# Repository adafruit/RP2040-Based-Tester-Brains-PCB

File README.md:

## Adafruit RP2040 Based Tester Brains PCB

PCB files for the Adafruit RP2040 Based Tester Brains. 

Format is EagleCAD schematic and board layout

### Description

This board is what we use internally at Adafruit to program and test boards with microcontrollers on them. 
   * An [RP2040 Pico](https://www.adafruit.com/product/5525) (or perhaps PicoW?) is used to run the test software
   * [Use a 16x2 LCD (ideally RGB backlight)](https://www.adafruit.com/product/398) for display output with color feedback such as green for pass, red for fail. RGB backlight is WS2811-controlled. Don't forget to set the contrast pot on first usage.
   * Serial1 hardware UART has RX/TX pin switch to flip directions
   * 1.9" TFT connector is placed but hasn't been tested or used yet
   * Piezo buzzer can be used for audible feedback alerts
   * STEMMA QT I2C port
   * Big reset button
   * Firmware files can be stored on MicroSD card which is slotted in. 
   * Connect the right hand side, either the 0.1" header or 18-pin EYESPI-like FPC connector to the device-under-test jig which can be different for each product. 
   * [USB Host testing is done with bitbang PIO support in TinyUSB](https://github.com/adafruit/Adafruit_TinyUSB_Arduino), USB 5V power can be turned on / off 
   * Use Philhower RP2040 core for programming
   * The RP2040 brains can perform ESP32 programming, RP2040-via-USB, AVR ICSP/UPDI, or SWD DAP. [See the TestBed library for some examples.](https://github.com/adafruit/Adafruit_TestBed)

**THIS IS NOT AN ADAFRUIT PRODUCT, IT IS COMPLETELY AND UTTERLY UNSUPPORTED. THERE ARE NO PLANS/ETA FOR MANUFACTURING, STOCKING OR SUPPORTING. DO NOT ASK FOR SUPPORT OR ASSISTANCE. THIS INCLUDES ASKING US FOR BOM, SOURCING OR ASSEMBLY HELP. WE DON'T GUARANTEE IT WORKS FOR YOU OR AT ALL AND ARE ONLY PUBLISHING IT IN THE HOPES THAT IT IS USEFUL FOR SOMEONE WHO DOES NOT NEED SUPPORT OR ASSISTANCE IN USING IT!**

### License

Adafruit invests time and resources providing this open source design, please support Adafruit and open-source hardware by purchasing products from [Adafruit](https://www.adafruit.com)!

Designed by Limor Fried/Ladyada for Adafruit Industries.

Creative Commons Attribution/Share-Alike, all text above must be included in any redistribution. 
See license.txt for additional details.

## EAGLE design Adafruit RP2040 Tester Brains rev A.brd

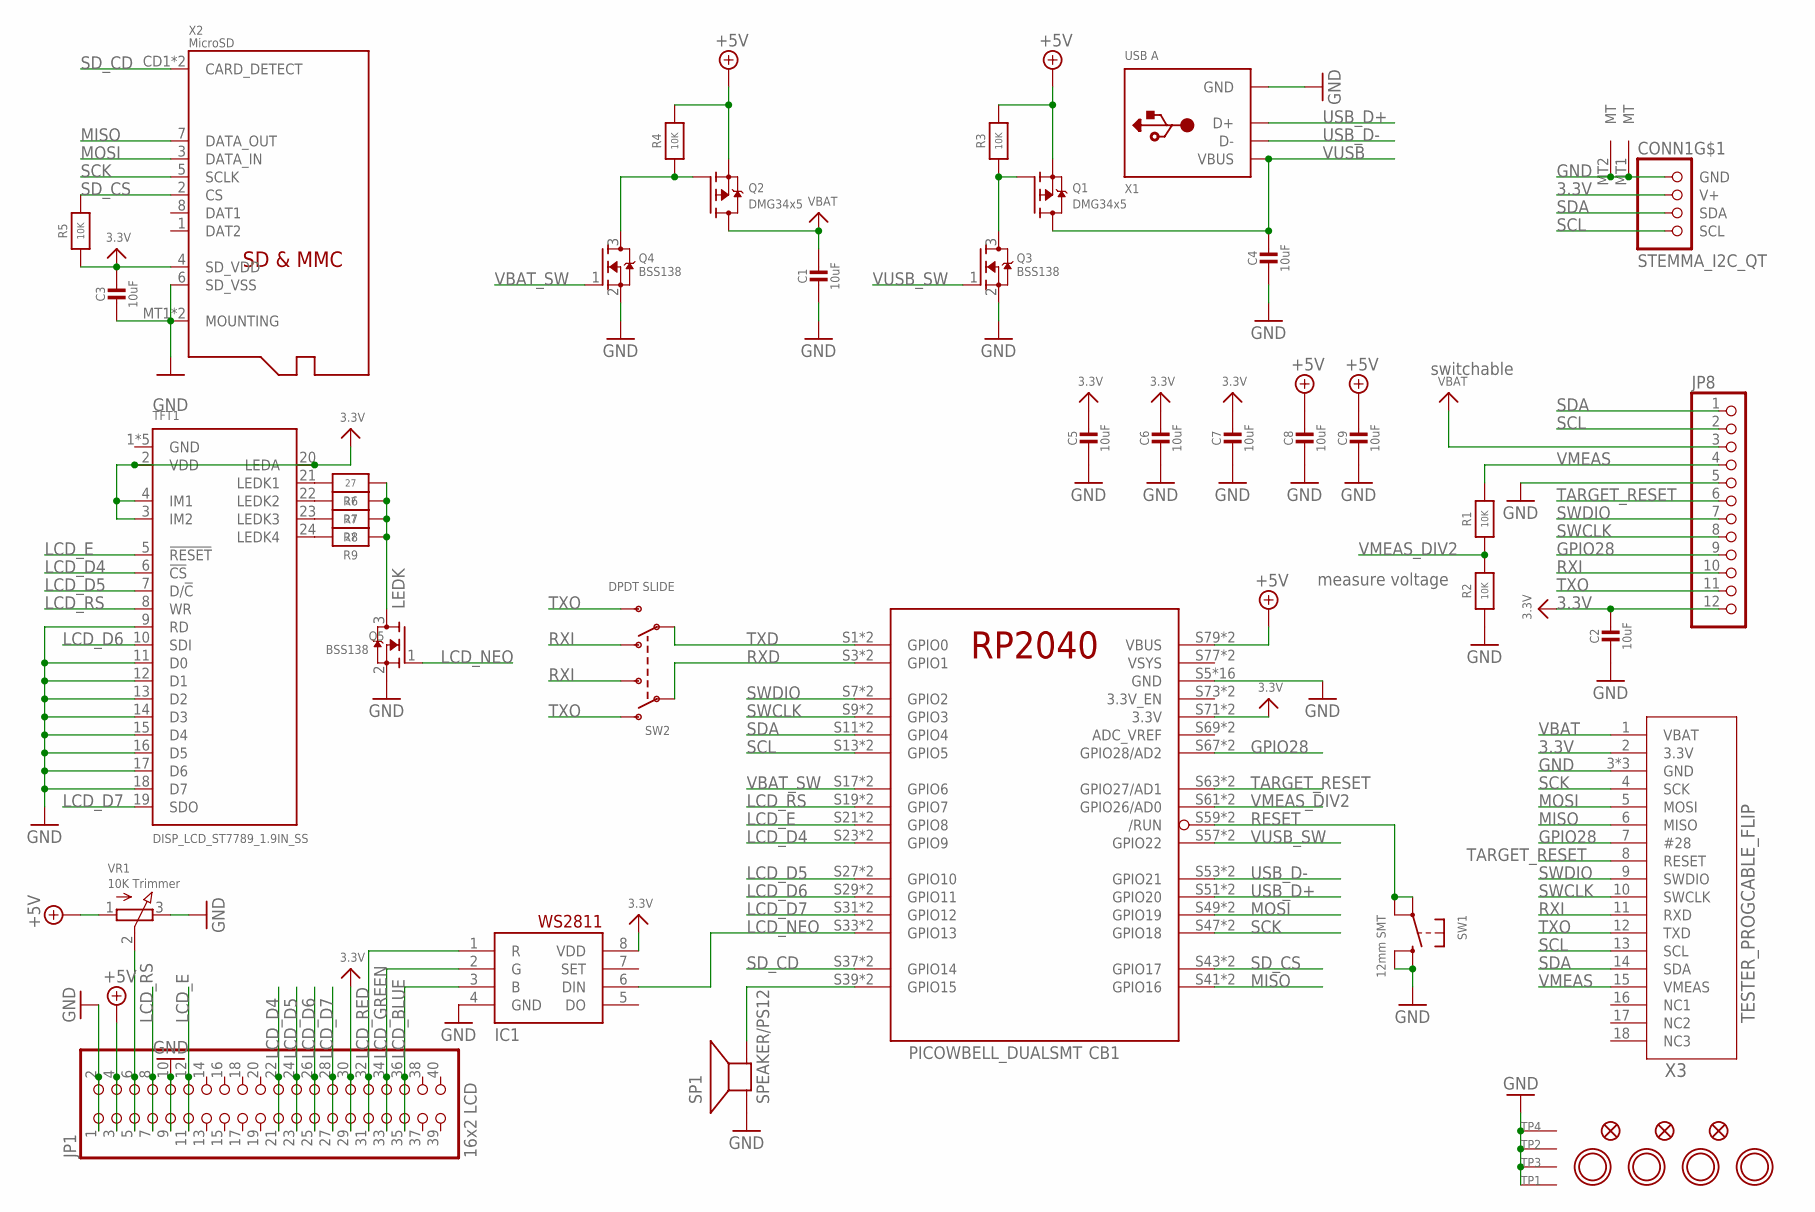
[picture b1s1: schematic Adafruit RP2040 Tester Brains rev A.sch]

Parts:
C1, C2, C3, C4, C5, C6, C7, C8, C9: 10uF; 0805-NO
CB1: PICOWBELL_DUALSMT
CONN1: STEMMA_I2C_QT; JST_SH4
FID1, FID2, FID3: FIDUCIAL_1MM
IC1: WS2811-SOP8; SO08-SKINNYPADS
JP1: 16x2 LCD; 2X20_SMT_MALE
JP8: HEADER-1X12OVAL; 1X12_OVAL
Q1, Q2: DMG34x5; SOT23-WIDE
Q3, Q4, Q5: BSS138; SOT23-WIDE
R1, R2, R3, R4, R5: 10K; 0603-NO
R6, R7, R8, R9: 27; 0603-NO; LCSC C25190
SP1: SPEAKER/PS12; PS12
SW1: 12mm SMT; B3F-40XX-SMT
SW2: DPDT SLIDE; EG1390; LCSC C318999
TFT1: DISP_LCD_ST7789_1.9IN_SS; TFT_1.9IN_170X320_30P_SS
TP1, TP2, TP3, TP4: SEWTAP_SMTNUTM3; SMT_NUT_3MM
U$7, U$8, U$9, U$10: MOUNTINGHOLE3.0THIN; MOUNTINGHOLE_3.0_PLATEDTHIN
VR1: 10K Trimmer; TRIMPOT_BOURNS_TC33X-2
X1: USB A; USB_HOST-SMT
X2: MicroSD; MICROSD
X3: TESTER_PROGCABLE_FLIP; FPC_0.5MM_18PIN

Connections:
3.3V: C2.1, C3.1, C5.1, C6.1, C7.1, CB1.S71 (3.3V), CB1.S72 (3.3V), CONN1.2 (V+), IC1.8 (VDD), JP1.29, JP1.30, JP8.12, R5.1, TFT1.2 (VDD), TFT1.3 (IM2), TFT1.4 (IM1), TFT1.20 (LEDA), X2.4 (SD_VDD), X3.2 (3.3V)
!VBAT_SW1: Q2.1 (G), Q4.3 (D), R4.1
!VBAT_SW2: Q1.1 (G), Q3.3 (D), R3.1
+5V: C8.1, C9.1, CB1.S79 (VBUS), CB1.S80 (VBUS), JP1.3, JP1.4, Q1.2 (S), Q2.2 (S), R3.2, R4.2, VR1.1 (A)
GND: C1.2, C2.2, C3.2, C4.2, C5.2, C6.2, C7.2, C8.2, C9.2, CB1.S5 (GND), CB1.S6 (GND), CB1.S15 (GND), CB1.S16 (GND), CB1.S25 (GND), CB1.S26 (GND), CB1.S35 (GND), CB1.S36 (GND), CB1.S45 (GND), CB1.S46 (GND), CB1.S55 (GND), CB1.S56 (GND), CB1.S65 (GND), CB1.S66 (GND), CB1.S75 (GND), CB1.S76 (GND), CONN1.1 (GND), CONN1.MT1 (MT), CONN1.MT2 (MT), IC1.4 (GND), JP1.1, JP1.2, JP1.9, JP1.10, JP8.5, Q3.2 (S), Q4.2 (S), Q5.2 (S), R2.1, SP1.P$1 (+), SW1.P$3 (S), SW1.P$4 (S1), TFT1.1 (GND), TFT1.9 (RD), TFT1.11 (D0), TFT1.12 (D1), TFT1.13 (D2), TFT1.14 (D3), TFT1.15 (D4), TFT1.16 (D5), TFT1.17 (D6), TFT1.18 (D7), TFT1.25 (GND), TFT1.30 (GND), TFT1.MNT1 (GND), TFT1.MNT2 (GND), TP1.P$1, TP2.P$1, TP3.P$1, TP4.P$1, VR1.3 (E), X1.GND, X2.6 (SD_VSS), X2.MT1 (MOUNTING), X2.MT2 (MOUNTING), X3.3 (GND), X3.SUPPORT1 (GND), X3.SUPPORT2 (GND)
GPIO28: CB1.S67 (GPIO28/AD2), CB1.S68 (GPIO28/AD2), JP8.9, X3.7 (#28)
LCD_BLUE: IC1.3 (B), JP1.35, JP1.36
LCD_D4: CB1.S23 (GPIO9), CB1.S24 (GPIO9), JP1.21, JP1.22, TFT1.6 (!CS)
LCD_D5: CB1.S27 (GPIO10), CB1.S28 (GPIO10), JP1.23, JP1.24, TFT1.7 (D/!C)
LCD_D6: CB1.S29 (GPIO11), CB1.S30 (GPIO11), JP1.25, JP1.26, TFT1.10 (SDI)
LCD_D7: CB1.S31 (GPIO12), CB1.S32 (GPIO12), JP1.27, JP1.28, TFT1.19 (SDO)
LCD_E: CB1.S21 (GPIO8), CB1.S22 (GPIO8), JP1.11, JP1.12, TFT1.5 (!RESET)
LCD_GREEN: IC1.2 (G), JP1.33, JP1.34
LCD_NEO: CB1.S33 (GPIO13), CB1.S34 (GPIO13), IC1.6 (DIN), Q5.1 (G)
LCD_RED: IC1.1 (R), JP1.31, JP1.32
LCD_RS: CB1.S19 (GPIO7), CB1.S20 (GPIO7), JP1.7, JP1.8, TFT1.8 (WR)
LEDK: Q5.3 (D), R6.1, R7.1, R8.1, R9.1
MISO: CB1.S41 (GPIO16), CB1.S42 (GPIO16), X2.7 (DATA_OUT), X3.6 (MISO)
MOSI: CB1.S49 (GPIO19), CB1.S50 (GPIO19), X2.3 (DATA_IN), X3.5 (MOSI)
unnamed: CB1.S39 (GPIO15), CB1.S40 (GPIO15), SP1.P$2 (-)
unnamed: R6.2, TFT1.21 (LEDK1)
unnamed: R7.2, TFT1.22 (LEDK2)
unnamed: R8.2, TFT1.23 (LEDK3)
unnamed: R9.2, TFT1.24 (LEDK4)
unnamed: JP1.5, JP1.6, VR1.2 (S)
RESET: CB1.S59 (/RUN), CB1.S60 (/RUN), SW1.P$1, SW1.P$2 (P1)
RXD: CB1.S3 (GPIO1), CB1.S4 (GPIO1), SW2.P1
RXI: JP8.10, SW2.O2, SW2.S1, X3.11 (RXD)
SCK: CB1.S47 (GPIO18), CB1.S48 (GPIO18), X2.5 (SCLK), X3.4 (SCK)
SCL: CB1.S13 (GPIO5), CB1.S14 (GPIO5), CONN1.4 (SCL), JP8.2, X3.13 (SCL)
SDA: CB1.S11 (GPIO4), CB1.S12 (GPIO4), CONN1.3 (SDA), JP8.1, X3.14 (SDA)
SD_CD: CB1.S37 (GPIO14), CB1.S38 (GPIO14), X2.CD1 (CARD_DETECT), X2.CD2 (CARD_DETECT)
SD_CS: CB1.S43 (GPIO17), CB1.S44 (GPIO17), R5.2, X2.2 (CS)
SWCLK: CB1.S9 (GPIO3), CB1.S10 (GPIO3), JP8.8, X3.10 (SWCLK)
SWDIO: CB1.S7 (GPIO2), CB1.S8 (GPIO2), JP8.7, X3.9 (SWDIO)
TARGET_RESET: CB1.S63 (GPIO27/AD1), CB1.S64 (GPIO27/AD1), JP8.6, X3.8 (RESET)
TXD: CB1.S1 (GPIO0), CB1.S2 (GPIO0), SW2.P2
TXO: JP8.11, SW2.O1, SW2.S2, X3.12 (TXD)
USB_D+: CB1.S51 (GPIO20), CB1.S52 (GPIO20), X1.D+
USB_D-: CB1.S53 (GPIO21), CB1.S54 (GPIO21), X1.D-
VBAT: C1.1, JP8.3, Q2.3 (D), X3.1 (VBAT)
VBAT_SW: CB1.S17 (GPIO6), CB1.S18 (GPIO6), Q4.1 (G)
VMEAS: JP8.4, R1.2, X3.15 (VMEAS)
VMEAS_DIV2: CB1.S61 (GPIO26/AD0), CB1.S62 (GPIO26/AD0), R1.1, R2.2
VSYS: CB1.S77 (VSYS), CB1.S78 (VSYS)
VUSB: C4.1, Q1.3 (D), X1.VBUS
VUSB_SW: CB1.S57 (GPIO22), CB1.S58 (GPIO22), Q3.1 (G)

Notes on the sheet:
switchable
measure voltage

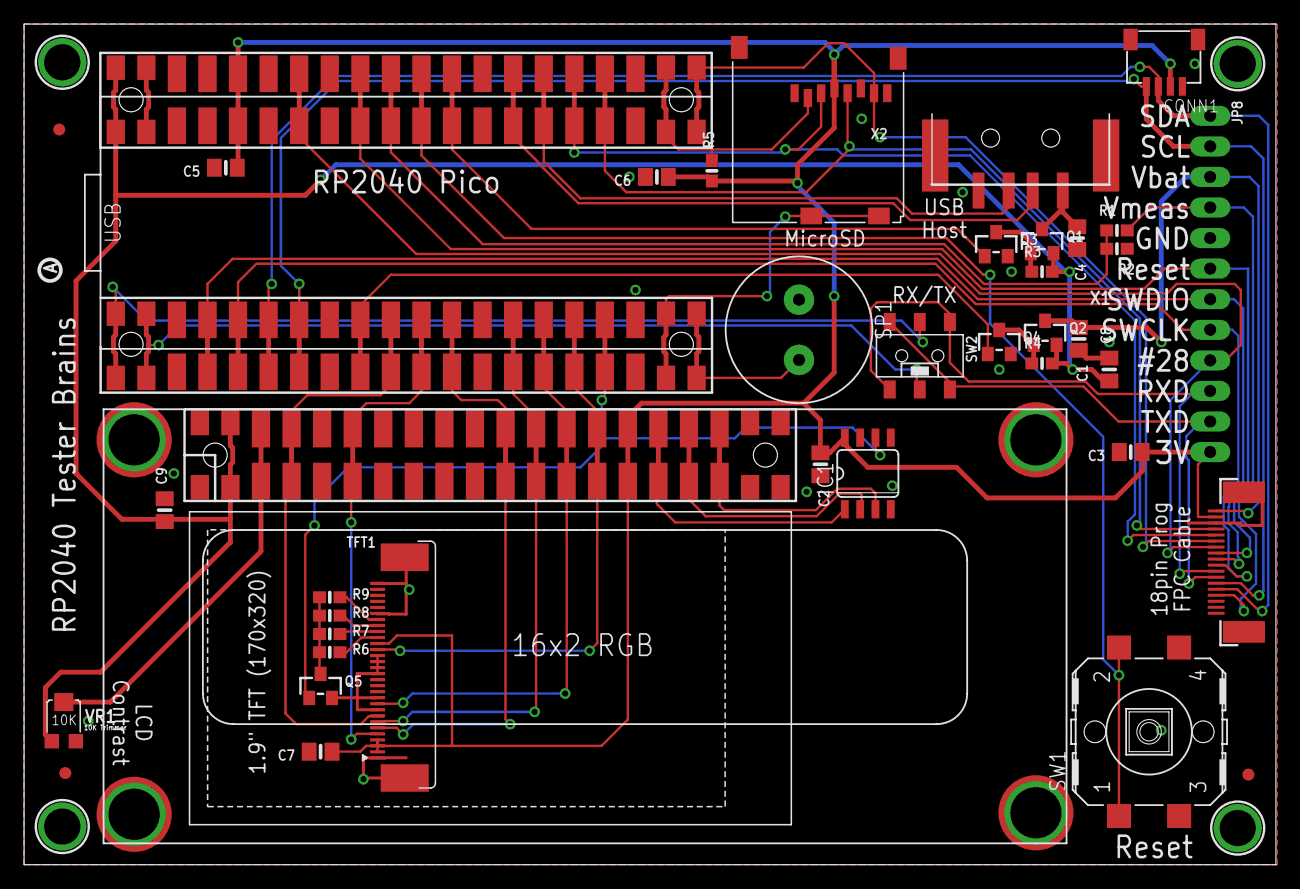
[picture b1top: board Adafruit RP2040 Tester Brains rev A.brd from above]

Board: 2 copper layers, 104.0 x 69.8 mm, 48 parts (0 on the bottom side), 47 nets.

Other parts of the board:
U$13: PCBFEAT-REV-040

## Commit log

2023-02-16 Fixed embeds
2023-02-16 Moved test.uf2
2023-02-16 Update README.md
    linx
2023-02-16 Update README.md
    ok but is it supported?
2023-02-16 Update README.md
    bullets

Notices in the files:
parts and their libraries:
microbuilder: This work is placed in the public domain, and may be freely used for commercial and non-commercial work with the following conditions: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
